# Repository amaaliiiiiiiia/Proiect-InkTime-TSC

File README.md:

# Proiect-InkTime-TSC
### Diagrama Bloc

## Tabel BOM (Bill of Materials)

| Componenta | Referinta | Link | Datasheet |
| :--- | :---: | :--- | :--- |
| **nRF52840-QFAA-F-R7** | `U1` | [JLC Parts](https://jlcpcb.com/partdetail/NordicSemicon-NRF52840_QFAA_FR7/C3606653) | [Datasheet](https://octopart.com/datasheet/nordic-semiconductor/NRF52840-QFAA-F-R7) |
| **MAX17048G+T10** | `U3` | [JLC Parts](https://jlcpcb.com/partdetail/2777647-MAX17048GT10/C2682616) | [Datasheet](https://www.analog.com/media/en/technical-documentation/data-sheets/MAX17048-MAX17049.pdf) |
| **BQ25180YBGR** | `IC1` | [JLC Parts](https://jlcpcb.com/partdetail/TexasInstruments-BQ25180YBGR/C3682423) | [Datasheet](https://www.alldatasheet.com/datasheet-pdf/view/1359210/TI/BQ25180YBGR.html) |
| **RT6160AWSC** | `IC2` | [JLC Parts](https://jlcpcb.com/partdetail/RichtekTech-RT6160AWSC/C7065276) | [Datasheet](https://www.alldatasheet.com/datasheet-pdf/view/1709403/RICHTEK/RT6160AWSC.html) |
| **BMA423** | `IC3` | [JLC Parts](https://jlcpcb.com/partdetail/BoschSensortec-BMA423/C189517) | [Datasheet](https://watchy.sqfmi.com/assets/files/BST-BMA423-DS000-1509600-950150f51058597a6234dd3eaafbb1f0.pdf) |
| **DRV2605YZFR** | `IC4` | [JLC Parts](https://jlcpcb.com/partdetail/TexasInstruments-DRV2605YZFR/C81079) | [Datasheet](https://www.ti.com/lit/ds/symlink/drv2605.pdf) |
| **2450AT18B100E** | `ANT1` | [JLC Parts](https://jlcpcb.com/partdetail/JohansonDielectrics-2450AT18B100E/C2917717) | [Datasheet](https://www.johansontechnology.com/datasheets/2450AT18B100/2450AT18B100.pdf) |
| **NX2016SA-32MHZ** | `X1` | [JLC Parts](https://jlcpcb.com/partdetail/NDK-NX2016SA_32MHZ_EXS00ACS06654/C5441424) | [Datasheet](https://mm.digikey.com/Volume0/opasdata/d220001/medias/docus/6749/CS11213-32M.pdf) |
| **ABS07-32.768KHZ** | `X2` | [JLC Parts](https://jlcpcb.com/partdetail/AbraconLLC-ABS07_32_768KHZT/C130253) | [Datasheet](https://abracon.com/Resonators/ABS07.pdf) |
| **ATFC-0201-1N0-B-T** | `L1, L2, L3` | [JLC Parts](https://jlcpcb.com/partdetail/AbraconLLC-ATFC_0201_1N0BT/C2042148) | [Datasheet](https://www.alldatasheet.com/datasheet-pdf/view/244743/ABRACON/ATFC-0201-1N0-BT.html) |
| **744043680** | `L5` | [JLC Parts](https://jlcpcb.com/partdetail/WurthElektronik-744043680/C2045671) | [Datasheet](https://www.we-online.com/catalog/datasheet/744043680.pdf) |
| **MLP2016SR47MT0S1** | `L7` | [JLC Parts](https://jlcpcb.com/parts/componentSearch?searchTxt=MLP2016SR47MT0S1) | [Datasheet](https://product.tdk.com/en/system/files/dam/doc/product/inductor/inductor/smd/catalog/inductor_commercial_power_mlp2016_en.pdf) |
| **DMG2305UX-7** | `Q1` | [JLC Parts](https://jlcpcb.com/partdetail/DiodesIncorporated-DMG2305UX7/C150470) | [Datasheet](https://www.mouser.com/datasheet/2/115/DMG2305UX-266242.pdf?srsltid=AfmBOopbVRXA0Ms8OtbeWgu2ogF1WUYsuFqvrexXW_fBru-Bf8ygnQco) |
| **SI1308EDL-T1-GE3** | `Q3` | [JLC Parts](https://jlcpcb.com/partdetail/VishayIntertech-SI1308EDL_T1GE3/C469327) | [Datasheet](https://www.vishay.com/docs/63399/si1308edl.pdf) |
| **MBR0530** | `D2, D4, D5` | [JLC Parts](https://jlcpcb.com/partdetail/78464-MBR0530/C77336) | [Datasheet](https://www.onsemi.com/pdf/datasheet/mbr0530t1-d.pdf) |
| **USBLC6-2SC6Y** | `D3` | [JLC Parts](https://jlcpcb.com/partdetail/STMicroelectronics-USBLC62SC6Y/C2969755) | [Datasheet](https://www.st.com/resource/en/datasheet/usblc6-2.pdf) |
| **503480-2400** | `J1` | [JLC Parts](https://jlcpcb.com/partdetail/MOLEX-5034802400/C122434) | [Datasheet](https://www.molex.com/pdm_docs/sd/5034802400_sd.pdf) |
| **KH-TYPE-C-16P** | `J4` | [SnapEda](https://www.snapeda.com/parts/KH-TYPE-C-16P/Kinghelm/view-part/) | [Datasheet](https://www.snapeda.com/parts/KH-TYPE-C-16P/kinghelm/datasheet/) |
| **EVP-AKE31A** | `SW_ENT, SW_UP, SW_DN` | [JLC Parts](https://jlcpcb.com/parts/componentSearch?searchTxt=EVP-AKE31A) | [Datasheet](https://www.rxelectronics.fr/datasheet/19/evp-ake31a.pdf) |
| **02016D105KAT4A** | `0201 Capacitors` | [JLC Parts](http://jlcpcb.com/partdetail/-02016D105KAT2A/C5853878) | [Datasheet](https://datasheets.kyocera-avx.com/cx5r-KGM.pdf) |
| **0402B472K500NT** | `0402 Capacitors` | [JLC Parts](https://jlcpcb.com/partdetail/1890-0402B472K500NT/C1538) | [Datasheet](https://www.lcsc.com/datasheet/C1538.pdf?spm=wm.sxq.inf.ggs&lcsc_vid=ElJZBAJSEgJdXlJTFVMMBVQEFgdcUQYFRwVYXwZQTlAxVlNRQVZeV1NWRlJYVTsOAxUeFF5JWBYZEEoBGA4JCwFIFA4DSA%3D%3D) |
| **0603N101Z160PHT** | `0603 Capacitors` | [JLC Parts](https://jlcpcb.com/partdetail/1943-CL10B104KB8NNNC/C1591) | [Datasheet](https://static.chipdip.ru/lib/970/DOC041970475.pdf) |
| **CPF0201D7K68C1** | `0201 Resistors` | [JLC Parts](https://jlcpcb.com/partdetail/TEConnectivity-CPF0201D10KC1/C4187156) | [Datasheet](https://www.snapeda.com/parts/CPF0201D4K75E1/TE%20Connectivity/datasheet/) |

## Functionalitatea Hardware
#### MCU
- Componenta: Nordic Semiconductor nRF52840
- Specificatii: Nucleu ARM Cortex-M4 cu FPU la 64 MHz, 1MB Flash si 256KB RAM
- Este responsabil de sincronizarea datelor, interpretarea miscarii ceasului, optimizarea consumului de energie si redarea informatiilor pe display

#### Display E-Paper
- Conectat prin interfata SPI
- Este un afisaj bi-stabil, iar odata ce imaginea este formata de pixeli, ramane pe ecran fara sa necesite alimentare

#### Hapic Driver
- Conectat prin I2C
- Folosit pentru notificari, alarme, prin intermediul unui motor de vibratii de tip ERM

#### BMA423
- Conectat prin I2C
- Folosit pentru numararea pasilor si pentru detectarea miscarii mainii (tilt-to-wake)

#### Fuel Gauge (MAX17048)
- Conectat prin I2C
- Monitorizeaza tensiunea bateriei si ofera informatii despre starea de incarcare
- Nu are nevoie de rezistenta de sens, deci economisseste spatiu pe PCB

#### Sursa de energie
- Utilizarea unui LiPo Charger reincarcabil de 3.7V
- Asigura o autonomie de lunga durata datorita componentelor low-power folosite

#### Managementul Alimentarii
- BQ25180 gestioneaza incarcarea bateriei prin USB-C si ofera protectie la supra-tensiune si control termic
- Convertorul RT6160 asigura o tensiune constanta de 3.3V necesara componentelor
- Dioda USBLC6-2SC6Y protejeaza liniile de date USB impotriva descarcarilor electrostatice

## Pinii nRF52840
### Tabel Alocare Pini nRF52840

| Pin | Semnal / Functie | Explicatie |
| :--- | :--- | :--- |
| **P0.00 / P0.01** | XL1/XL2 | Conexiune pentru cristalul RTC de 32.768kHz, necesar pentru low-power timekeeping |
| **P0.02** | `SCK` | Clock pentru magistrala SPI, dedicat comunicatiei cu display-ul E-Paper |
| **P0.03** | `MOSI` | Linia de date Master Out Slave In pentru transferul imaginii catre display |
| **P0.05** | `EPD_CS` | Chip Select pentru activarea display-ului pe magistrala SPI |
| **P0.06** | `SDA` | Linia de date pentru magistrala I2C (partajata de BMA423, BQ25180, MAX17048) |
| **P0.07** | `SCL` | Linia de ceas pentru magistrala I2C |
| **P0.08** | `IMU_INT1` | Intrerupere primara de la BMA423 |
| **P0.10** | `ALERT` | Semnal de alerta |
| **P0.11** | `PMIC_INT` | Intrerupere de la IC-ul de management al bateriei |
| **P0.12** | `HAPTIC_EN` | Activeaza driverul DRV2605 |
| **P0.13** | `SW_UP` | Buton UP |
| **P0.14** | `SW_DN` | Buton DOWN |
| **P0.15** | `EPD_DC` | Data / Command select pentru display |
| **P0.16** | `EPD_RST` | Reset hardware pentru dispay |
| **P0.17** | `EPD_BUSY` | Statusul ecranului |
| **P0.18** | `RESET` | Reset general, legat la TC2030. |
| **P1.00** | `SW_ENT` | Buton ENTER |
| **P1.08** | `IMU_INT2` | Intrerupere secundara de la BMA423 |

## Justificarea Erorilor
Am acceptat cele 13 erori de tip Copper Clearance de pe componenta IC2 deoarece am prioritizat rutarea corecta a traseelor de tip 3V3, folosind 0.3mm.

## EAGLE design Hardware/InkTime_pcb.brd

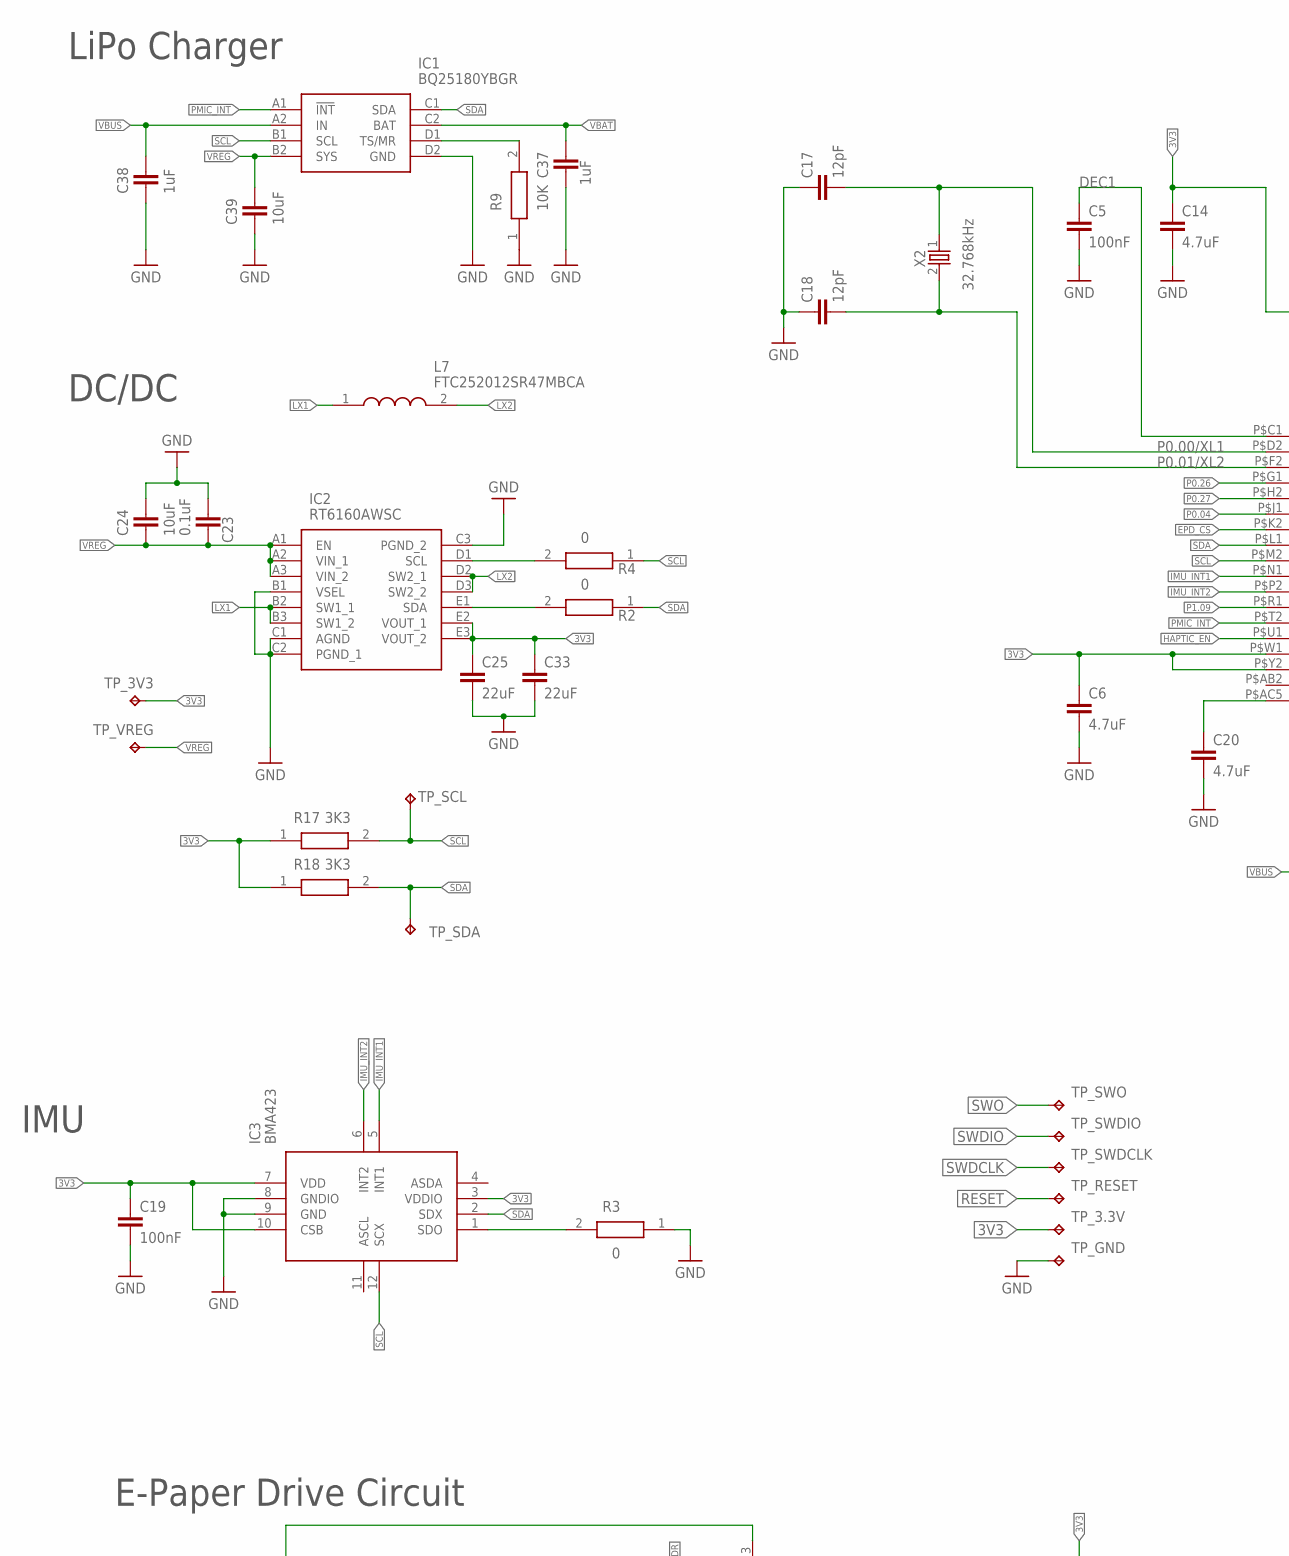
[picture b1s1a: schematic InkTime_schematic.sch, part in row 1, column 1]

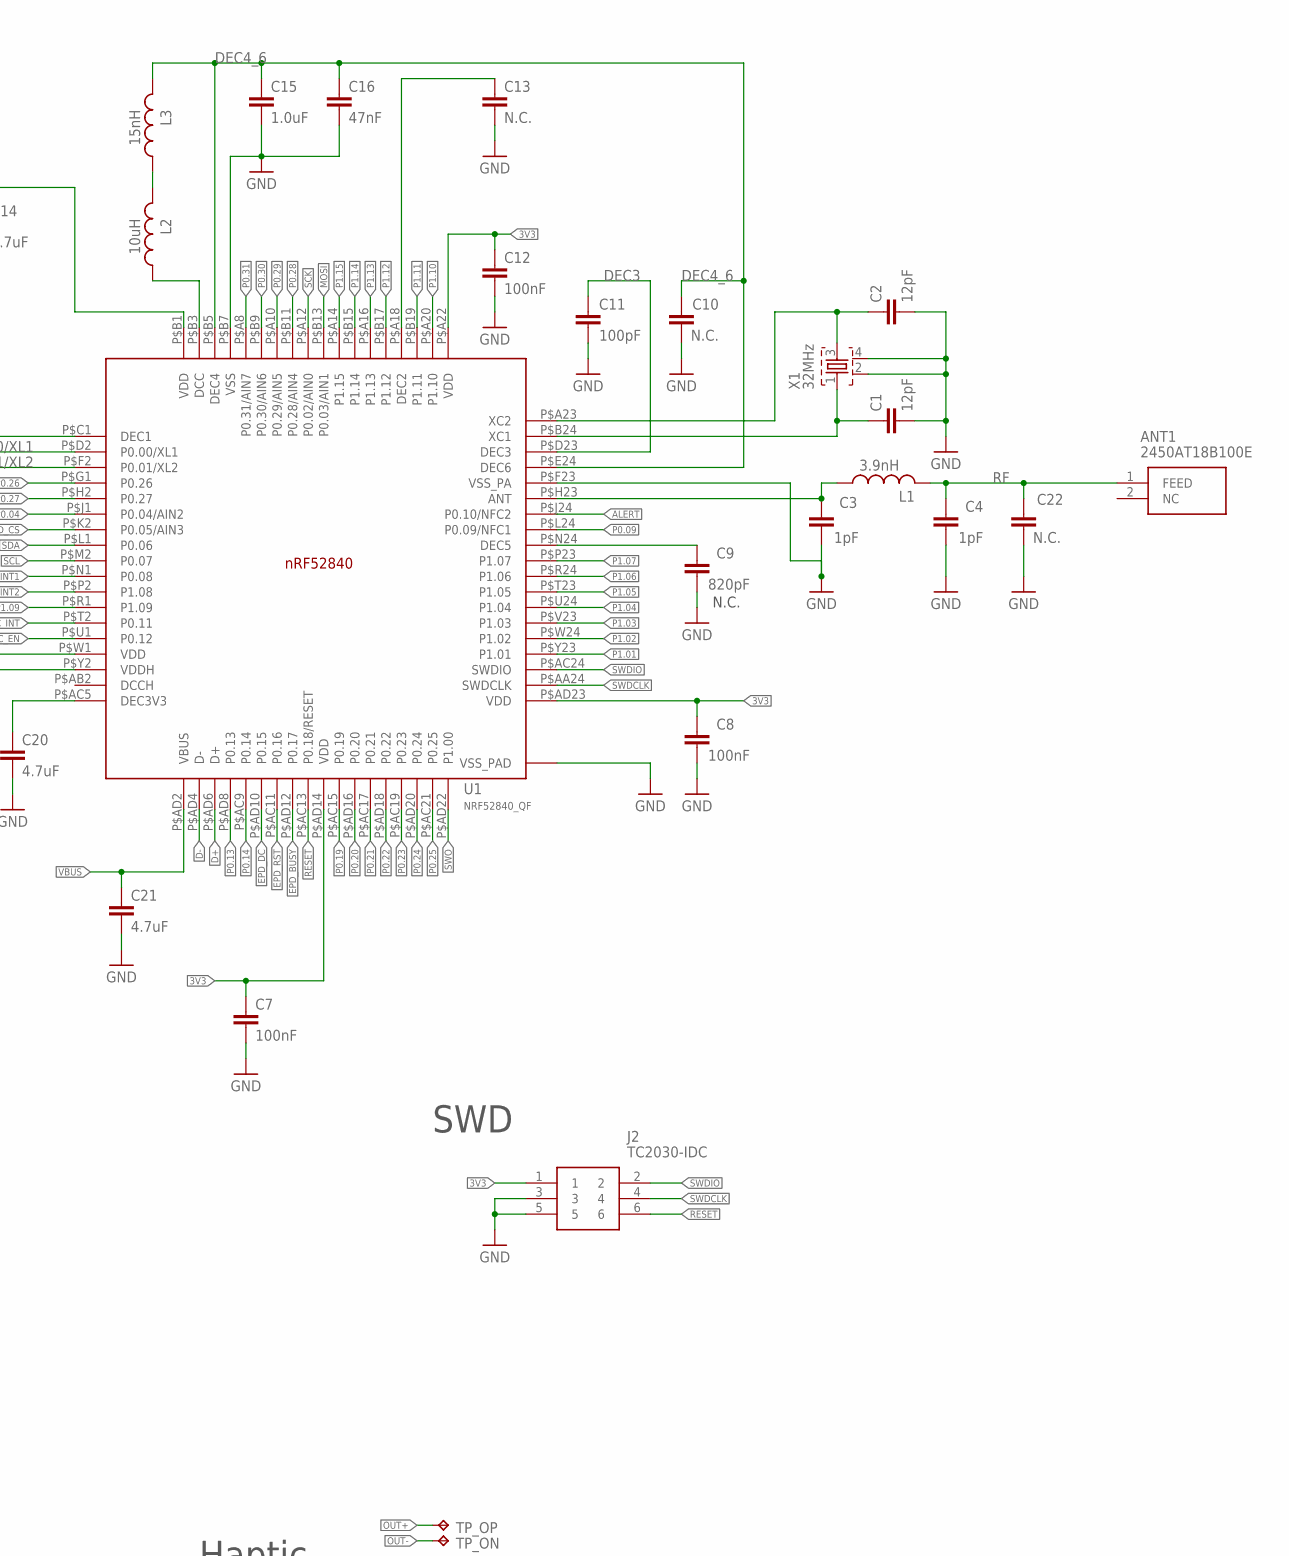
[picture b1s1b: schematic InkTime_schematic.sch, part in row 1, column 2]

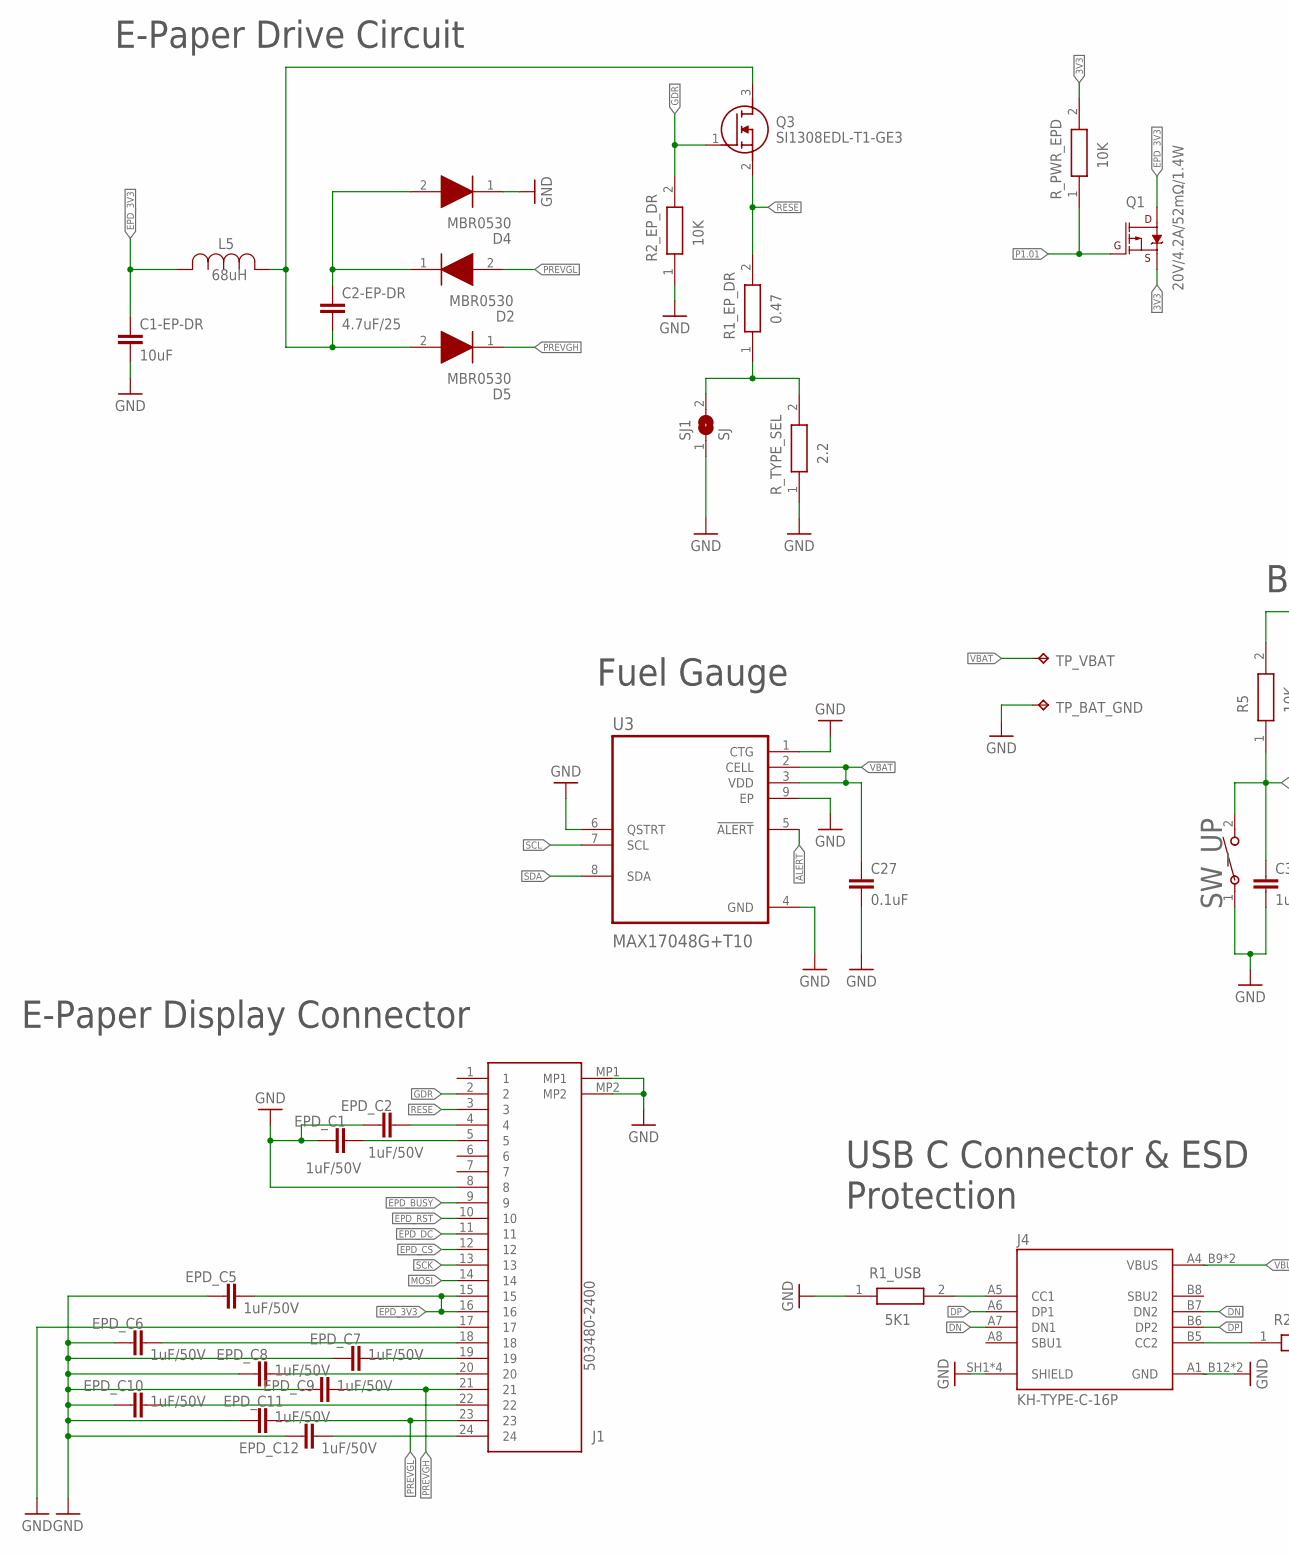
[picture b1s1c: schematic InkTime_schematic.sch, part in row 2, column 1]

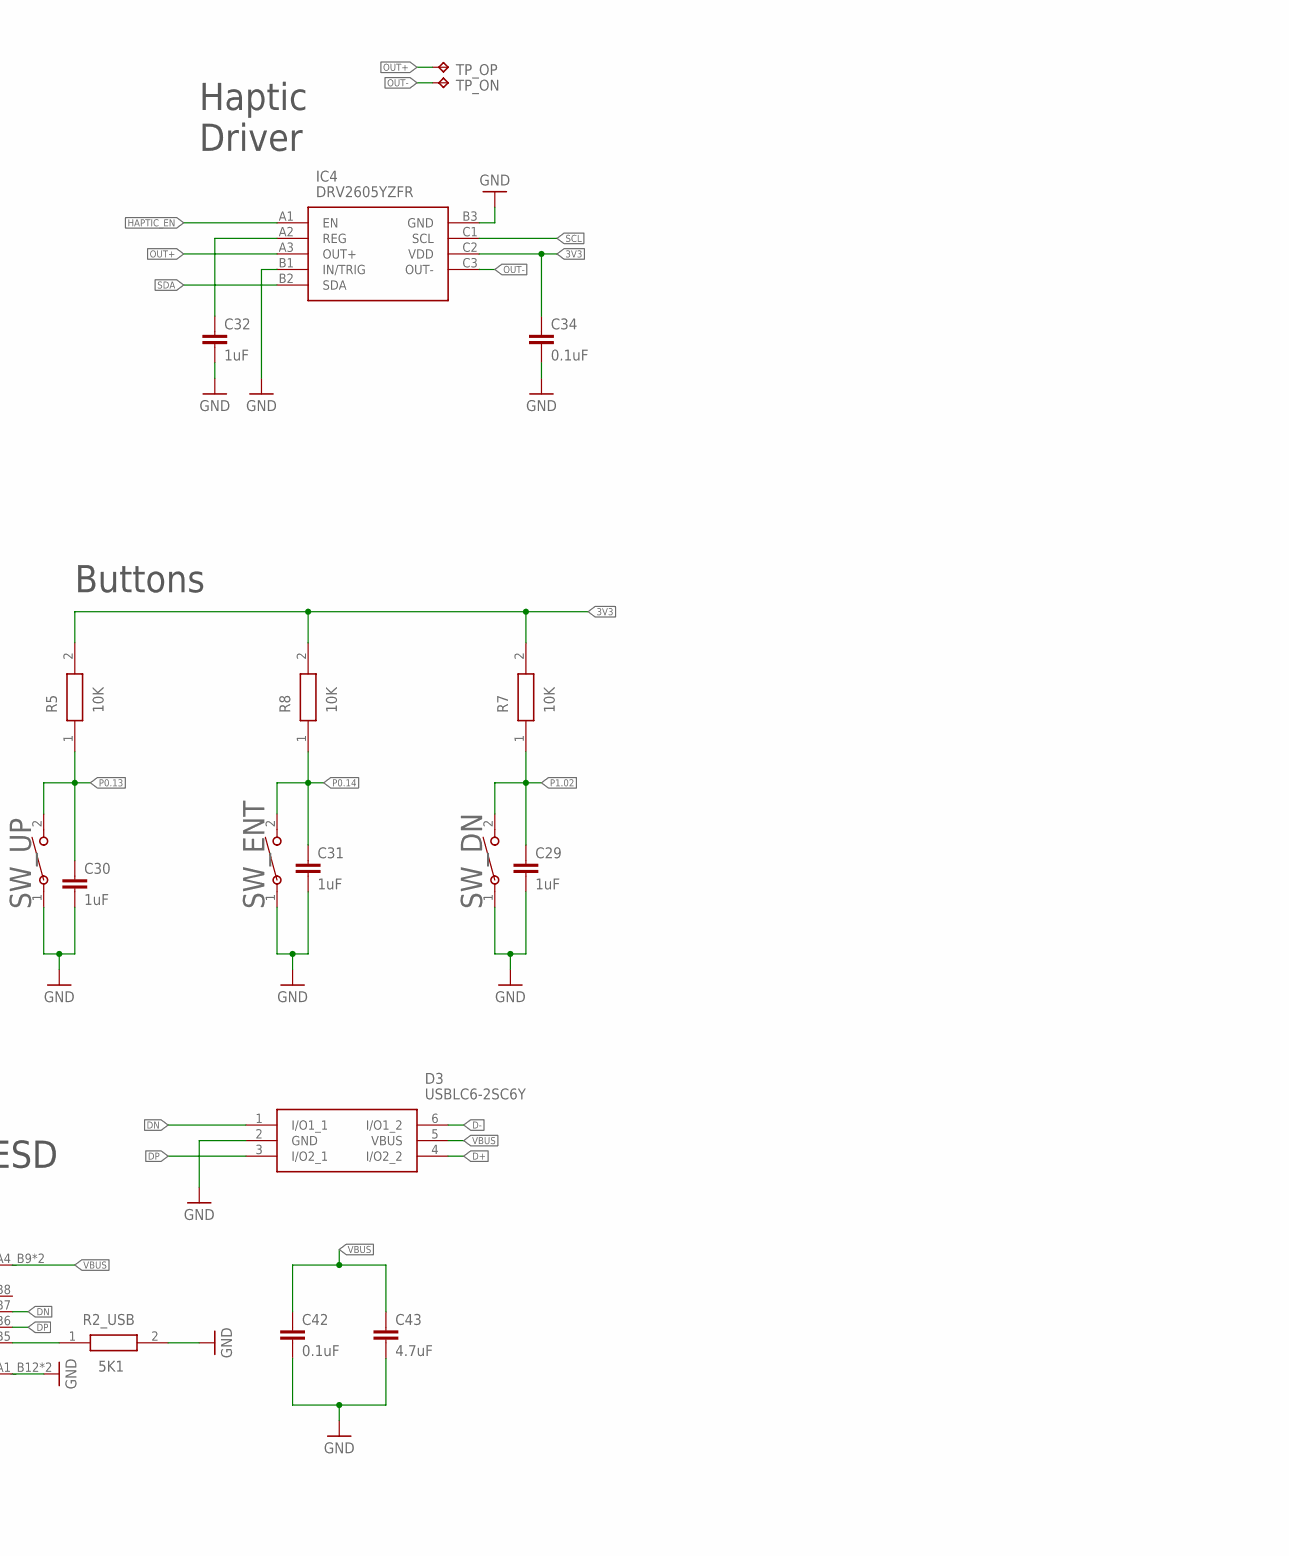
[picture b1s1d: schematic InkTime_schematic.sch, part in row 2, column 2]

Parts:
ANT1: 2450AT18B100E; 2450AT18B100E_ANTC3216X140N
C1, C2, C17, C18: 12pF; NORDIC_NRF_3_RESC0201_N
C1-EP-DR, C24, C39: 10uF; NORDIC_NRF_3_RESC0402_N
C2-EP-DR: 4.7uF/25; NORDIC_NRF_3_RESC0603_N
C3, C4: 1pF; NORDIC_NRF_3_RESC0201_N
C5, C7, C8, C12, C19: 100nF; NORDIC_NRF_3_RESC0201_N
C6, C14, C20, C21, C43: 4.7uF; NORDIC_NRF_3_RESC0402_N
C9: 820pF; NORDIC_NRF_3_RESC0201_N
C10, C13, C22: N.C.; NORDIC_NRF_3_RESC0201_N
C11: 100pF; NORDIC_NRF_3_RESC0201_N
C15: 1.0uF; NORDIC_NRF_3_RESC0402_N
C16: 47nF; NORDIC_NRF_3_RESC0201_N
C23, C27, C34, C42: 0.1uF; NORDIC_NRF_3_RESC0201_N
C25, C33: 22uF; NORDIC_NRF_3_RESC0402_N
C29, C30, C31, C32, C37, C38: 1uF; NORDIC_NRF_3_RESC0402_N
D2, D4, D5: MBR0530; ESP32_C6_LIBRARY_5_SOD3716X135N
D3: USBLC6-2SC6Y; ESP32_C6_LIBRARY_3_SOT95P280X145-6N
EPD_C1, EPD_C2, EPD_C5, EPD_C6, EPD_C7, EPD_C8, EPD_C9, EPD_C10, EPD_C11, EPD_C12: 1uF/50V; NORDIC_NRF_3_RESC0603_N
IC1: BQ25180YBGR; BQ25180YBGR_BGA8C40P2X4_100X155X50
IC2: RT6160AWSC; RT6160AWSC_BGA15C40P3X5_140X230X60
IC3: BMA423; BMA423_BMA423
IC4: DRV2605YZFR; DRV2605YZFR_BGA9C50P3X3_144X144X62
J1: 503480-2400; 503480-2400_5034802400
J2: TC2030-IDC; TC2030-IDC_TC2030IDC
J4: KH-TYPE-C-16P; KH-TYPE-C-16P_KINGHELM_KH-TYPE-C-16P
L1: 3.9nH; NORDIC_NRF_2_RESC0201_N
L2: 10uH; NORDIC_NRF_2_RESC0201_N
L3: 15nH; NORDIC_NRF_2_RESC0201_N
L5: 68uH; ESP32_C6_LIBRARY_2_IND_4828-WE-TPC_WRE
L7: FTC252012SR47MBCA; MLP2016SR47MT0S1_INDC2016X100N
Q1: 20V/4.2A/52mΩ/1.4W; ESP32_C6_LIBRARY_4_ESP32_C6_LIBRARY_4_ESP32_C6_LIBRARY_4_ES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
Q3: SI1308EDL-T1-GE3; ESP32_C6_LIBRARY_6_SOT65P210X110-3N
R1_EP_DR: 0.47; ERA-1AEB3401C_0201
R1_USB, R2_USB: 5K1; CPF0201D7K68C1_0201
R2, R4: 0; CPF0201D7K68C1_0201
R2_EP_DR, R5, R7, R8: 10K; ERA-1AEB3401C_0201
R3: 0; ERA-1AEB3401C_0201
R9: 10K; CPF0201D7K68C1_0201
R17, R18: 3K3; CPF0201D7K68C1_0201
R_PWR_EPD: 10K; CPF0201D7K68C1_0201
R_TYPE_SEL: 2.2; ERA-1AEB3401C_0201
SJ1: SJ; ESP32_C6_LIBRARY_7_JUMPER_SJ
SW_DN: SW_DN; 2025-10-22_07-23-44_LIBRARY_SW_EVP-AKE31A_PAN
SW_ENT: SW_ENT; 2025-10-22_07-23-44_LIBRARY_SW_EVP-AKE31A_PAN
SW_UP: SW_UP; 2025-10-22_07-23-44_LIBRARY_SW_EVP-AKE31A_PAN
TP_3.3V, TP_3V3: HECTOR_WATCH_1_TPTP20R; HECTOR_WATCH_1_TP20R
TP_BAT_GND: HECTOR_WATCH_1_TPTP20R; HECTOR_WATCH_1_TP20R
TP_GND: HECTOR_WATCH_1_TPTP20R; HECTOR_WATCH_1_TP20R
TP_ON: HECTOR_WATCH_1_TPTP20R; HECTOR_WATCH_1_TP20R
TP_OP: HECTOR_WATCH_1_TPTP20R; HECTOR_WATCH_1_TP20R
TP_RESET: HECTOR_WATCH_1_TPTP20R; HECTOR_WATCH_1_TP20R
TP_SCL: HECTOR_WATCH_1_TPTP20R; HECTOR_WATCH_1_TP20R
TP_SDA: HECTOR_WATCH_1_TPTP20R; HECTOR_WATCH_1_TP20R
TP_SWDCLK: HECTOR_WATCH_1_TPTP20R; HECTOR_WATCH_1_TP20R
TP_SWDIO: HECTOR_WATCH_1_TPTP20R; HECTOR_WATCH_1_TP20R
TP_SWO: HECTOR_WATCH_1_TPTP20R; HECTOR_WATCH_1_TP20R
TP_VBAT: HECTOR_WATCH_1_TPTP20R; HECTOR_WATCH_1_TP20R
TP_VREG: HECTOR_WATCH_1_TPTP20R; HECTOR_WATCH_1_TP20R
U1: NRF52840_QF; NORDIC_NRF_4_AQFN50P700X700X85_HS-74N
U3: MAX17048G+T10; ESP32_C6_LIBRARY_SON50P200X200X80-9N
X1: 32MHz; NORDIC_NRF_BT-XTAL_2016_N
X2: 32.768kHz; NORDIC_NRF_1_XTAL_3215_N

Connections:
3V3: C6.1, C7.1, C8.2, C12.1, C14.1, C19.1, C25.1, C33.1, C34.1, IC2.E2 (VOUT_1), IC2.E3 (VOUT_2), IC3.3 (VDDIO), IC3.7 (VDD), IC3.10 (CSB), IC4.C2 (VDD), J2.1, Q1.2 (S), R5.2, R7.2, R8.2, R17.1, R18.1, R_PWR_EPD.2, TP_3.3V.TP, TP_3V3.TP, U1.P$A22 (VDD), U1.P$AD14 (VDD), U1.P$AD23 (VDD), U1.P$B1 (VDD), U1.P$W1 (VDD), U1.P$Y2 (VDDH)
ALERT: U1.P$J24 (P0.10/NFC2), U3.5 (!ALERT)
D+: D3.4 (I/O2_2), U1.P$AD6 (D+)
D-: D3.6 (I/O1_2), U1.P$AD4 (D-)
DEC1: C5.1, U1.P$C1 (DEC1)
DEC3: C11.2, U1.P$D23 (DEC3)
DEC4_6: C10.2, C15.1, C16.1, L3.2, U1.P$B5 (DEC4), U1.P$E24 (DEC6)
DN: D3.1 (I/O1_1), J4.A7 (DN1), J4.B7 (DN2)
DP: D3.3 (I/O2_1), J4.A6 (DP1), J4.B6 (DP2)
EPD_3V3: C1-EP-DR.1, EPD_C5.2, J1.15, J1.16, L5.2, Q1.3 (D)
EPD_BUSY: J1.9, U1.P$AD12 (P0.17)
EPD_CS: J1.12, U1.P$K2 (P0.05/AIN3)
EPD_DC: J1.11, U1.P$AD10 (P0.15)
EPD_RST: J1.10, U1.P$AC11 (P0.16)
GDR: J1.2, Q3.1 (G), R2_EP_DR.2
GND: C1.2, C1-EP-DR.2, C2.2, C3.1, C4.1, C5.2, C6.2, C7.2, C8.1, C9.1, C10.1, C11.1, C12.2, C13.2, C14.2, C15.2, C16.2, C17.1, C18.1, C19.2, C20.2, C21.2, C22.2, C23.1, C24.1, C25.2, C27.2, C29.2, C30.2, C31.2, C32.2, C33.2, C34.2, C37.2, C38.2, C39.2, C42.2, C43.2, D3.2 (GND), D4.1 (K), EPD_C1.1, EPD_C2.1, EPD_C5.1, EPD_C6.1, EPD_C7.1, EPD_C8.1, EPD_C9.1, EPD_C10.1, EPD_C11.1, EPD_C12.1, IC1.D2 (GND), IC2.B1 (VSEL), IC2.C1 (AGND), IC2.C2 (PGND_1), IC2.C3 (PGND_2), IC3.8 (GNDIO), IC3.9 (GND), IC4.B1 (IN/TRIG), IC4.B3 (GND), J1.8, J1.17, J1.MP1, J1.MP2, J2.3, J2.5, J4.A1_B12 (GND), J4.A12_B1 (GND), J4.SH1 (SHIELD), J4.SH2 (SHIELD), J4.SH3 (SHIELD), J4.SH4 (SHIELD), R1_USB.1, R2_EP_DR.1, R2_USB.2, R3.1, R9.1, R_TYPE_SEL.1, SJ1.1, SW_DN.1, SW_ENT.1, SW_UP.1, TP_BAT_GND.TP, TP_GND.TP, U1.P$74 (VSS_PAD), U1.P$75 (VSS_PAD), U1.P$76 (VSS_PAD), U1.P$77 (VSS_PAD), U1.P$78 (VSS_PAD), U1.P$79 (VSS_PAD), U1.P$80 (VSS_PAD), U1.P$81 (VSS_PAD), U1.P$82 (VSS_PAD), U1.P$83 (VSS_PAD), U1.P$84 (VSS_PAD), U1.P$85 (VSS_PAD), U1.P$86 (VSS_PAD), U1.P$87 (VSS_PAD), U1.P$88 (VSS_PAD), U1.P$89 (VSS_PAD), U1.P$90 (VSS_PAD), U1.P$B7 (VSS), U1.P$F23 (VSS_PA), U3.1 (CTG), U3.4 (GND), U3.6 (QSTRT), U3.9 (EP), X1.2, X1.4
HAPTIC_EN: IC4.A1 (EN), U1.P$U1 (P0.12)
IMU_INT1: IC3.5 (INT1), U1.P$N1 (P0.08)
IMU_INT2: IC3.6 (INT2), U1.P$P2 (P1.08)
LX1: IC2.B2 (SW1_1), IC2.B3 (SW1_2), L7.1
LX2: IC2.D2 (SW2_1), IC2.D3 (SW2_2), L7.2
MOSI: J1.14, U1.P$B13 (P0.03/AIN1)
unnamed: C1.1, U1.P$B24 (XC1), X1.1
unnamed: C2.1, U1.P$A23 (XC2), X1.3
unnamed: C3.2, L1.1, U1.P$H23 (ANT)
unnamed: C9.2, U1.P$N24 (DEC5)
unnamed: C13.1, U1.P$A18 (DEC2)
unnamed: IC2.D1 (SCL), R4.2
unnamed: L2.1, U1.P$B3 (DCC)
unnamed: L2.2, L3.1
unnamed: C20.1, U1.P$AC5 (DEC3V3)
unnamed: EPD_C2.2, J1.4
unnamed: IC1.D1 (TS/MR), R9.2
unnamed: IC2.E1 (SDA), R2.2
unnamed: C32.1, IC4.A2 (REG)
unnamed: R1_EP_DR.1, R_TYPE_SEL.2, SJ1.2
unnamed: IC3.1 (SDO), R3.2
unnamed: C2-EP-DR.1, D2.1 (K), D4.2 (A)
unnamed: C2-EP-DR.2, D5.2 (A), L5.1, Q3.3 (D)
unnamed: EPD_C1.2, J1.5
unnamed: J4.B5 (CC2), R2_USB.1
unnamed: J4.A5 (CC1), R1_USB.2
unnamed: EPD_C6.2, J1.18
unnamed: EPD_C7.2, J1.19
unnamed: EPD_C8.2, J1.20
unnamed: EPD_C10.2, J1.22
unnamed: EPD_C12.2, J1.24
OUT+: IC4.A3 (OUT+), TP_OP.TP
OUT-: IC4.C3 (OUT-), TP_ON.TP
P0.00/XL1: C17.2, U1.P$D2 (P0.00/XL1), X2.1
P0.01/XL2: C18.2, U1.P$F2 (P0.01/XL2), X2.2
P0.04: U1.P$J1 (P0.04/AIN2)
P0.09: U1.P$L24 (P0.09/NFC1)
P0.13: C30.1, R5.1, SW_UP.2, U1.P$AD8 (P0.13)
P0.14: C31.1, R8.1, SW_ENT.2, U1.P$AC9 (P0.14)
P0.19: U1.P$AC15 (P0.19)
P0.20: U1.P$AD16 (P0.20)
P0.21: U1.P$AC17 (P0.21)
P0.22: U1.P$AD18 (P0.22)
P0.23: U1.P$AC19 (P0.23)
P0.24: U1.P$AD20 (P0.24)
P0.25: U1.P$AC21 (P0.25)
P0.26: U1.P$G1 (P0.26)
P0.27: U1.P$H2 (P0.27)
P0.28: U1.P$B11 (P0.28/AIN4)
P0.29: U1.P$A10 (P0.29/AIN5)
P0.30: U1.P$B9 (P0.30/AIN6)
P0.31: U1.P$A8 (P0.31/AIN7)
P1.01: Q1.1 (G), R_PWR_EPD.1, U1.P$Y23 (P1.01)
P1.02: C29.1, R7.1, SW_DN.2, U1.P$W24 (P1.02)
P1.03: U1.P$V23 (P1.03)
P1.04: U1.P$U24 (P1.04)
P1.05: U1.P$T23 (P1.05)
P1.06: U1.P$R24 (P1.06)
P1.07: U1.P$P23 (P1.07)
P1.09: U1.P$R1 (P1.09)
P1.10: U1.P$A20 (P1.10)
P1.11: U1.P$B19 (P1.11)
P1.12: U1.P$B17 (P1.12)
P1.13: U1.P$A16 (P1.13)
P1.14: U1.P$B15 (P1.14)
P1.15: U1.P$A14 (P1.15)
PMIC_INT: IC1.A1 (!INT), U1.P$T2 (P0.11)
PREVGH: D5.1 (K), EPD_C9.2, J1.21
PREVGL: D2.2 (A), EPD_C11.2, J1.23
RESE: J1.3, Q3.2 (S), R1_EP_DR.2
RESET: J2.6, TP_RESET.TP, U1.P$AC13 (P0.18/RESET)
RF: ANT1.1 (FEED), C4.2, C22.1, L1.2
SCK: J1.13, U1.P$A12 (P0.02/AIN0)
SCL: IC1.B1 (SCL), IC3.12 (SCX), IC4.C1 (SCL), R4.1, R17.2, TP_SCL.TP, U1.P$M2 (P0.07), U3.7 (SCL)
SDA: IC1.C1 (SDA), IC3.2 (SDX), IC4.B2 (SDA), R2.1, R18.2, TP_SDA.TP, U1.P$L1 (P0.06), U3.8 (SDA)
SWDCLK: J2.4, TP_SWDCLK.TP, U1.P$AA24 (SWDCLK)
SWDIO: J2.2, TP_SWDIO.TP, U1.P$AC24 (SWDIO)
SWO: TP_SWO.TP, U1.P$AD22 (P1.00)
VBAT: C27.1, C37.1, IC1.C2 (BAT), TP_VBAT.TP, U3.2 (CELL), U3.3 (VDD)
VBUS: C21.1, C38.1, C42.1, C43.1, D3.5 (VBUS), IC1.A2 (IN), J4.A4_B9 (VBUS), J4.A9_B4 (VBUS), U1.P$AD2 (VBUS)
VREG: C23.2, C24.2, C39.1, IC1.B2 (SYS), IC2.A1 (EN), IC2.A2 (VIN_1), IC2.A3 (VIN_2), TP_VREG.TP

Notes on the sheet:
N.C.
LiPo Charger
DC/DC
IMU
SWD
E-Paper Drive Circuit
E-Paper Display Connector
Fuel Gauge
Haptic Driver
Buttons
USB C Connector & ESD Protection

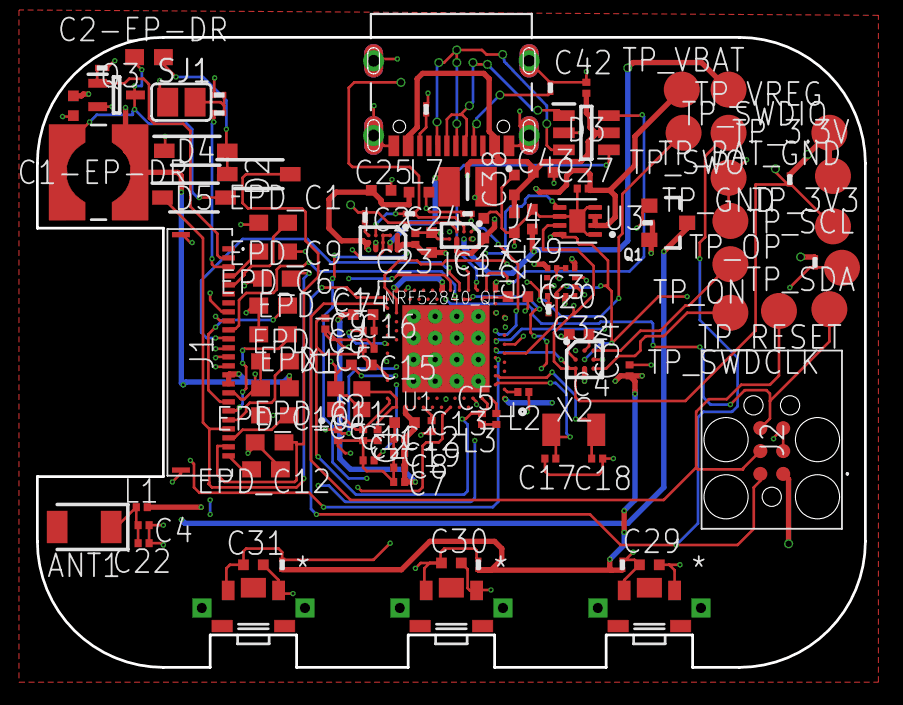
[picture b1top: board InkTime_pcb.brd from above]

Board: 4 copper layers, 46.0 x 35.0 mm, 105 parts (0 on the bottom side), 70 nets.

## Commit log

2026-04-10 schematic, pcb 2d
2026-04-10 pcb 3d
2026-04-10 randari pcb 3d
2026-04-10 pcb 3d .step
2026-04-13 Fisierele gerbers, .bom si .cpl
2026-04-13 schematic .pdf
2026-04-13 PCB + baterie + display + carcasa (exploded view si Fusion360)
2026-04-13 imagini dispozitiv final
2026-04-20 Diagrama si Tabel BOM in README
2026-04-20 Functionalitatea hardware
2026-04-20 Tabel Alocare Pini nRF52840 README
2026-04-20 Am rezolvat issue-urile din pcb 2d
2026-04-20 imagini
2026-04-20 Varianta finala
2026-04-20 Justificarea Erorilor README

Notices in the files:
parts and their libraries:
COPYRIGHT: Copyright (C) 2024 Ultra Librarian. All rights reserved.
COPYRIGHT: Copyright (C) 2025 Ultra Librarian. All rights reserved.
